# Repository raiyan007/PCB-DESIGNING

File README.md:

# PCB-DESIGNING USING EAGLE SOFTWARE
8 CHANNEL RELAY MODULE :
BOTH FILES OF SCHEMATIC AND BOARD HAVE BEEN UPLOADED

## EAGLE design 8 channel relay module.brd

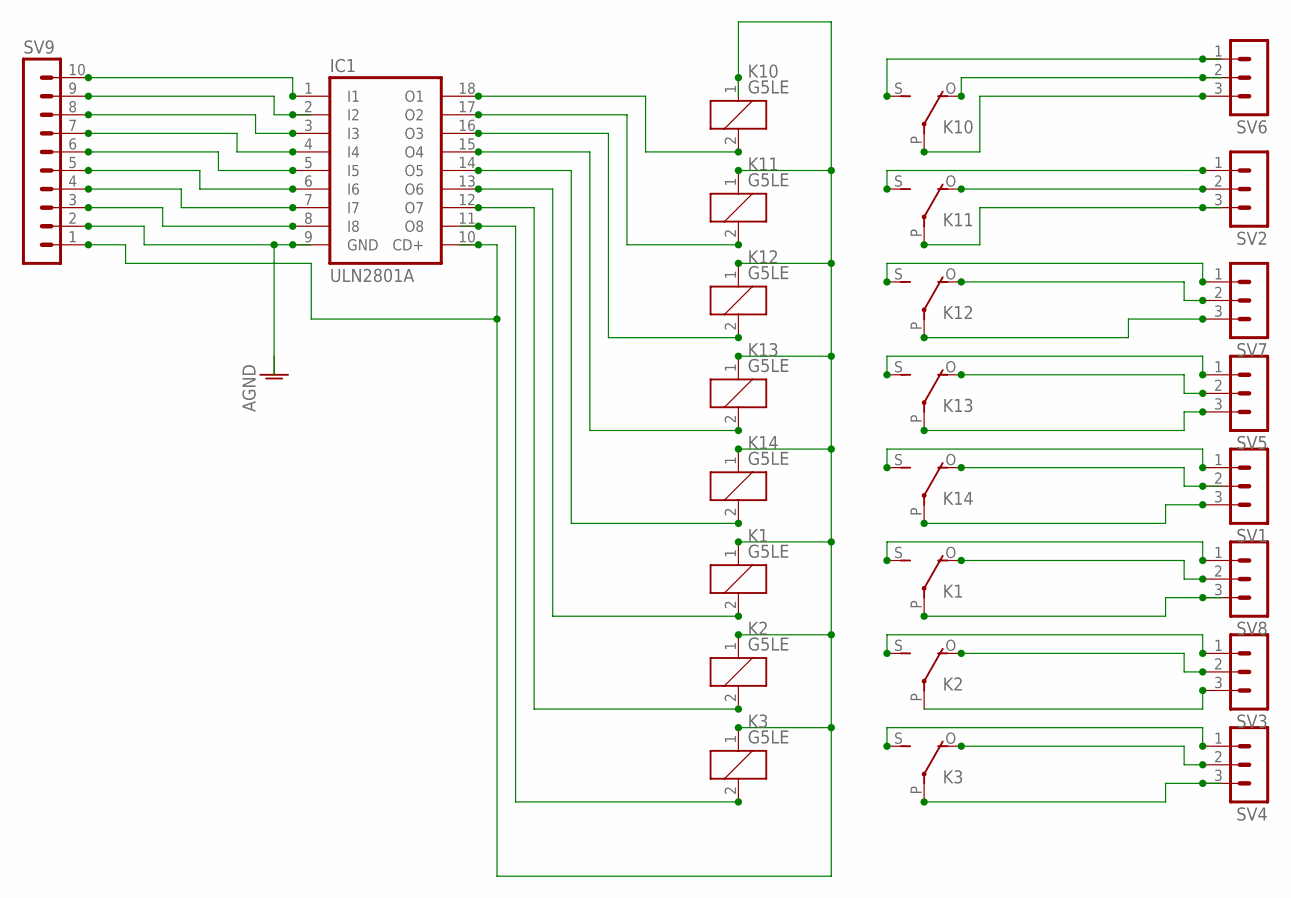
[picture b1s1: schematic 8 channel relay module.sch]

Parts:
IC1: ULN2801A; DIL18
K1, K2, K3, K10, K11, K12, K13, K14: G5LE
SV1, SV2, SV3, SV4, SV5, SV6, SV7, SV8: MA03-1
SV9: MA10-1

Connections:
unnamed: IC1.18 (O1), K10.2
unnamed: IC1.17 (O2), K11.2
unnamed: IC1.16 (O3), K12.2
unnamed: IC1.15 (O4), K13.2
unnamed: IC1.14 (O5), K14.2
unnamed: IC1.13 (O6), K1.2
unnamed: IC1.12 (O7), K2.2
unnamed: IC1.11 (O8), K3.2
unnamed: IC1.10 (CD+), K1.1, K2.1, K3.1, K10.1, K11.1, K12.1, K13.1, K14.1, SV9.1
unnamed: K10.S, SV6.1
unnamed: K10.P, SV6.3
unnamed: K10.O, SV6.2
unnamed: K11.S, SV2.1
unnamed: K11.O, SV2.2
unnamed: K11.P, SV2.3
unnamed: K12.S, SV7.1
unnamed: IC1.1 (I1), SV9.10
unnamed: K12.O, SV7.2
unnamed: K12.P, SV7.3
unnamed: K13.S, SV5.1
unnamed: K13.O, SV5.2
unnamed: K13.P, SV5.3
unnamed: K14.S, SV1.1
unnamed: K14.O, SV1.2
unnamed: K14.P, SV1.3
unnamed: K1.S, SV8.1
unnamed: K1.O, SV8.2
unnamed: K1.P, SV8.3
unnamed: K2.S, SV3.1
unnamed: K2.O, SV3.2
unnamed: K2.P, SV3.3
unnamed: K3.S, SV4.1
unnamed: IC1.2 (I2), SV9.9
unnamed: IC1.3 (I3), SV9.8
unnamed: IC1.4 (I4), SV9.7
unnamed: IC1.5 (I5), SV9.6
unnamed: IC1.6 (I6), SV9.5
unnamed: IC1.7 (I7), SV9.4
unnamed: IC1.8 (I8), SV9.3
unnamed: IC1.9 (GND), SV9.2
unnamed: K3.O, SV4.2
unnamed: K3.P, SV4.3

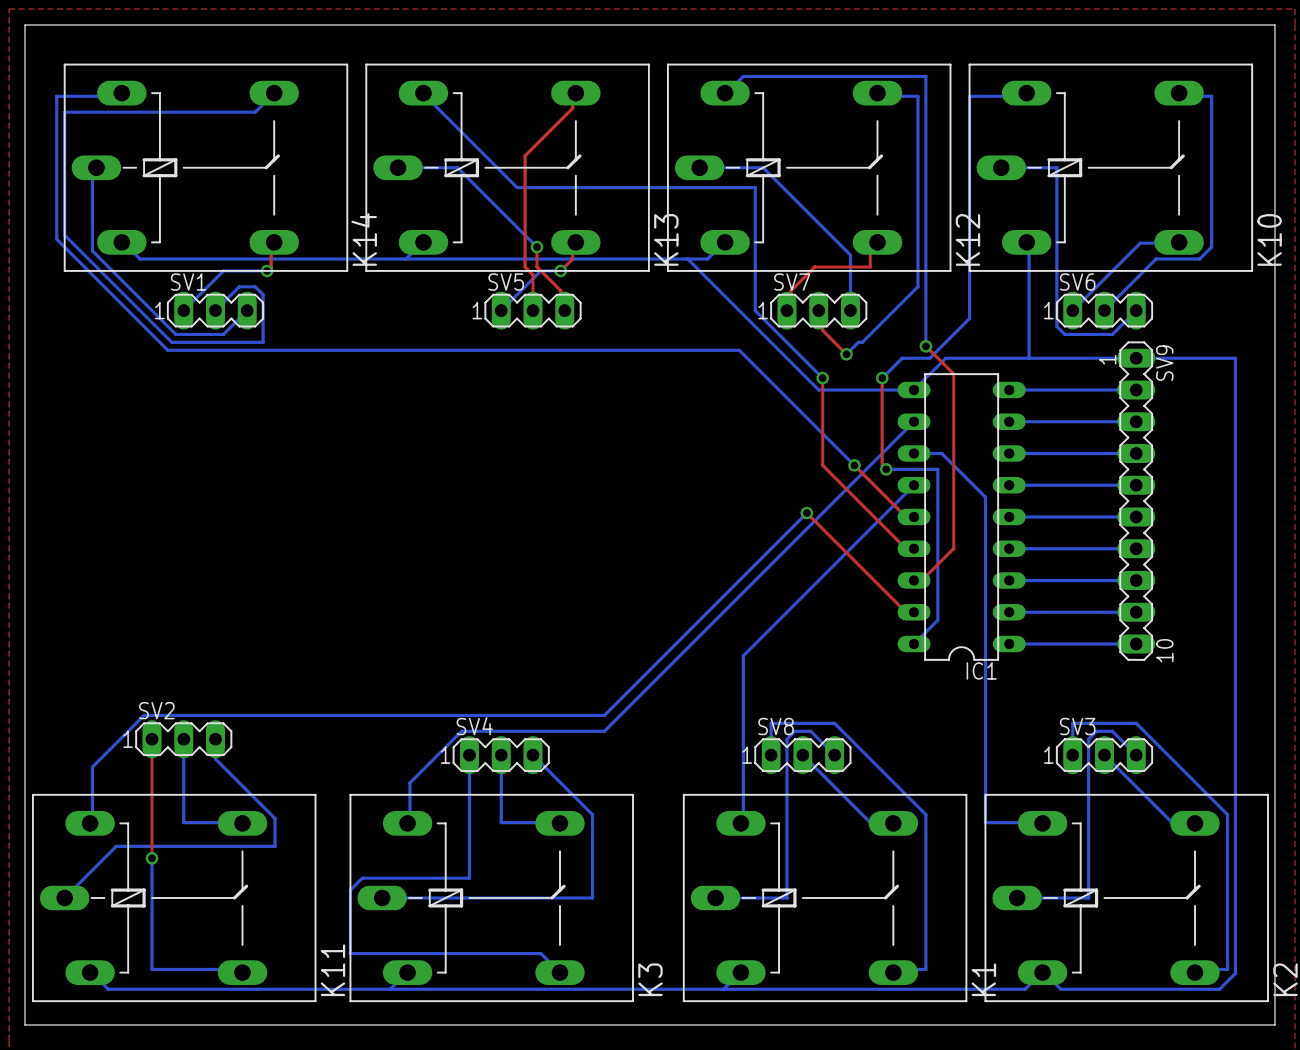
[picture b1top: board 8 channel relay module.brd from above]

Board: 2 copper layers, 100.0 x 80.0 mm, 18 parts (0 on the bottom side), 42 nets.
